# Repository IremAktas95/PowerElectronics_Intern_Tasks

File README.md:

# PowerElectronics_Intern_Tasks
Bu proje, 12V DC giriş gerilimini 24V DC (1A) çıkış gerilimine yükselten 24W kapasiteli bir Boost Converter tasarımıdır.

### Proje Özellikleri ve Yapılan Çalışmalar
* **Tasarım Parametreleri:** Sistem, 300 kHz anahtarlama frekansında ve Sürekli İletim Modunda CCM çalışacak şekilde tasarlanmıştır.
* **Simülasyon ve Hesaplamalar:** Belirlenen akım ve gerilim dalgalanma (ripple) kriterlerine uygun olarak filtre hesaplamaları yapılmış olup, devrenin çalışma prensibi ve kararlılığı LTspice ortamında gerçekleştirilen simülasyonlarla doğrulanmıştır.
* **Donanım ve PCB Tasarımı:** Simülasyonu tamamlanan devrenin KiCad kullanılarak şematik çizimi, PCB tasarımı ve 3D modellemesi yapılmıştır.
* **Üretim Hazırlığı:** Üretime hazır Gerber paketleri ve BOM (Malzeme Listesi) dosyaları oluşturulmuştur.

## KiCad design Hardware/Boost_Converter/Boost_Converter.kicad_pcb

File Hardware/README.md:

Bu klasör, Boost Converter projesinin KiCad şematik çizimlerini, PCB tasarımını, 3D görsellerini ve Gerber ile BOM dosyalarını içermektedir.

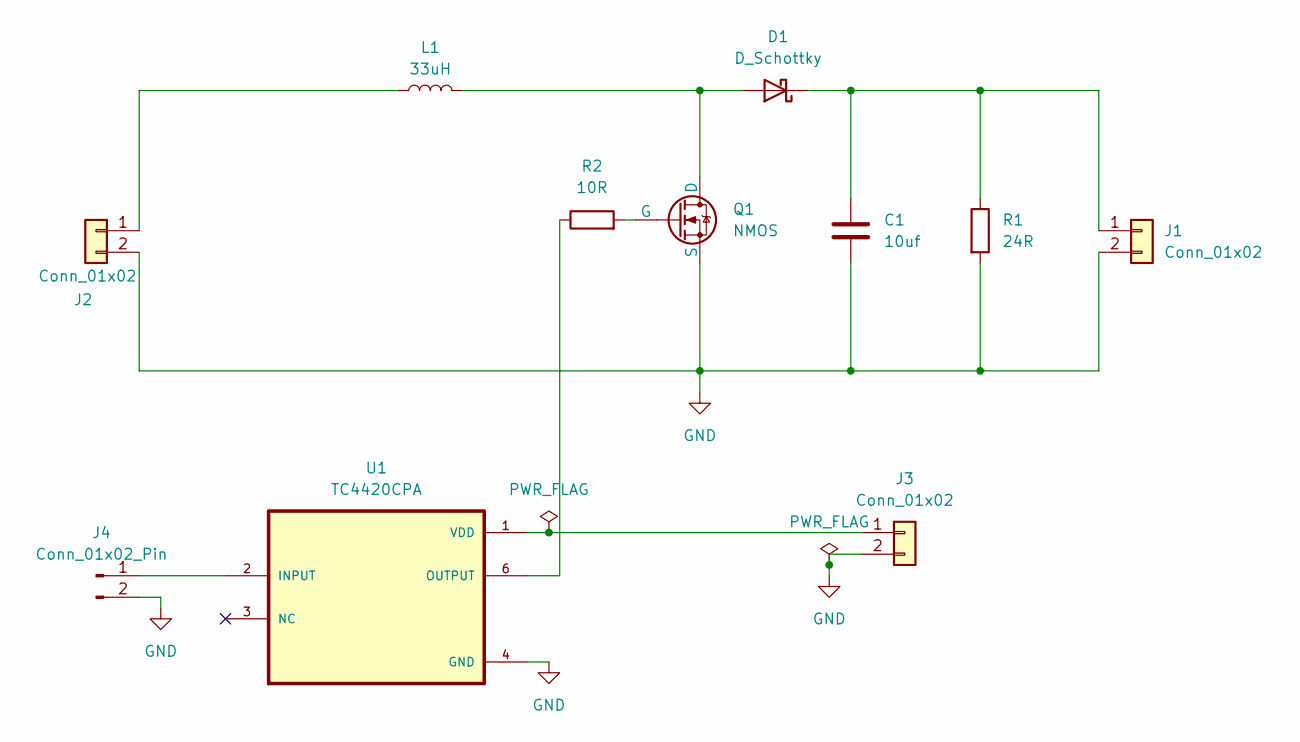
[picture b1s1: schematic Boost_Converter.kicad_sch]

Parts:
C1: 10uf; C_Rect_L26.5mm_W8.5mm_P22.50mm_MKS4
D1: D_Schottky; TO-220-2_Vertical
J1, J2, J3: Conn_01x02; TerminalBlock_Phoenix_MKDS-1,5-2_1x02_P5.00mm_Horizontal
J4: Conn_01x02_Pin; PinHeader_1x02_P2.54mm_Vertical
L1: 33uH; proje_bobin
Q1: NMOS; TO-220-3_Vertical
R1: 24R; R_Axial_DIN0207_L6.3mm_D2.5mm_P10.16mm_Horizontal
R2: 10R; R_Axial_DIN0207_L6.3mm_D2.5mm_P10.16mm_Horizontal
U1: TC4420CPA; DIP-8_W7.62mm

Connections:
GND: C1.2, J1.2, J2.2, J3.2, J4.2, Q1.3 (S), R1.2, U1.4 (GND), U1.5 (GND)
unnamed: D1.2 (A), L1.2, Q1.1 (D)
unnamed: C1.1, D1.1 (K), J1.1, R1.1
unnamed: J2.1, L1.1
unnamed: J4.1, U1.2 (INPUT)
unnamed: Q1.2 (G), R2.2
unnamed: R2.1, U1.6 (OUTPUT), U1.7 (OUTPUT)
VDD: J3.1, U1.1 (VDD), U1.8 (VDD)

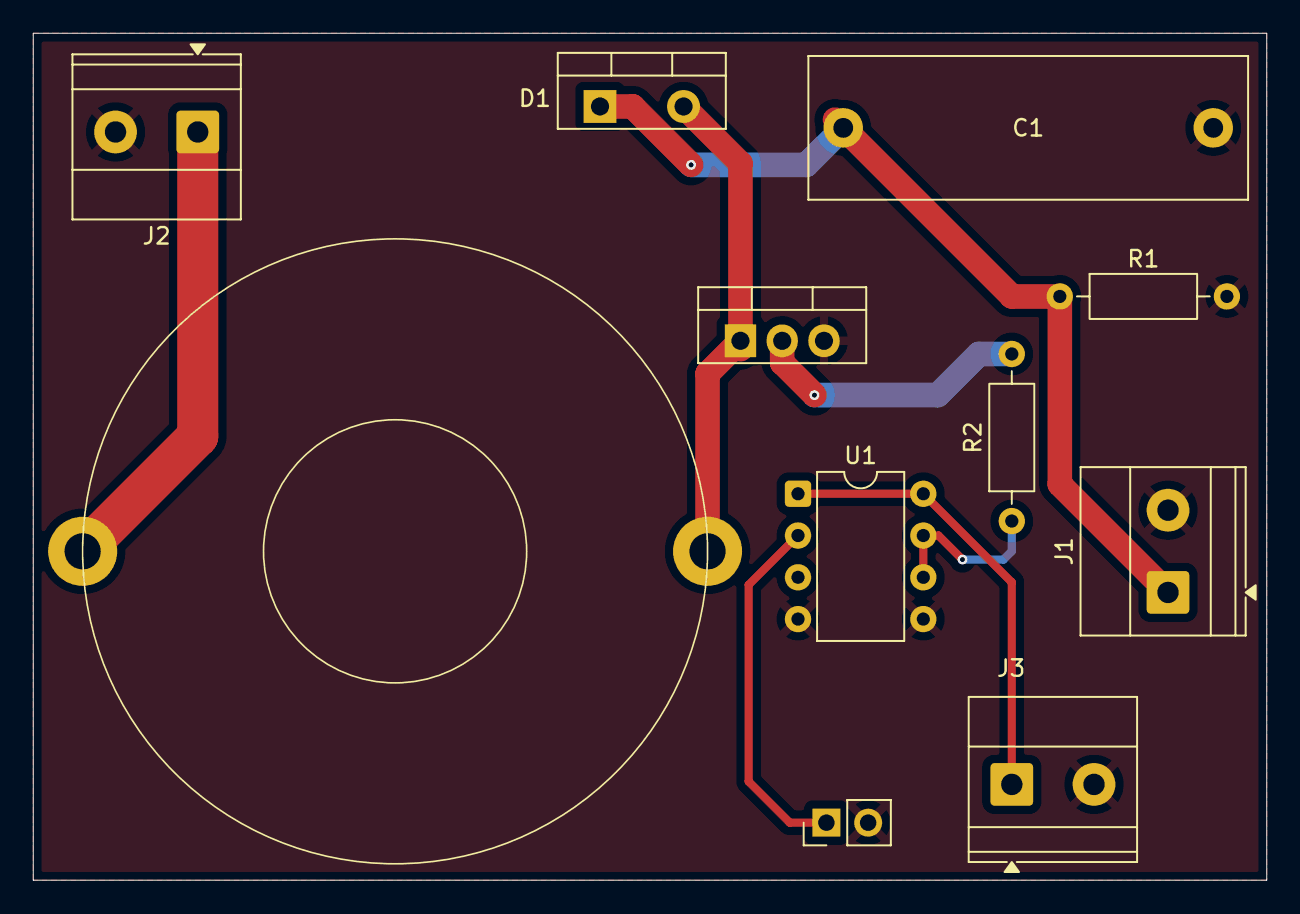
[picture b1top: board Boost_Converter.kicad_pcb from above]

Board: 2 copper layers, 75.0 x 51.5 mm, 11 parts (0 on the bottom side), 8 nets.
